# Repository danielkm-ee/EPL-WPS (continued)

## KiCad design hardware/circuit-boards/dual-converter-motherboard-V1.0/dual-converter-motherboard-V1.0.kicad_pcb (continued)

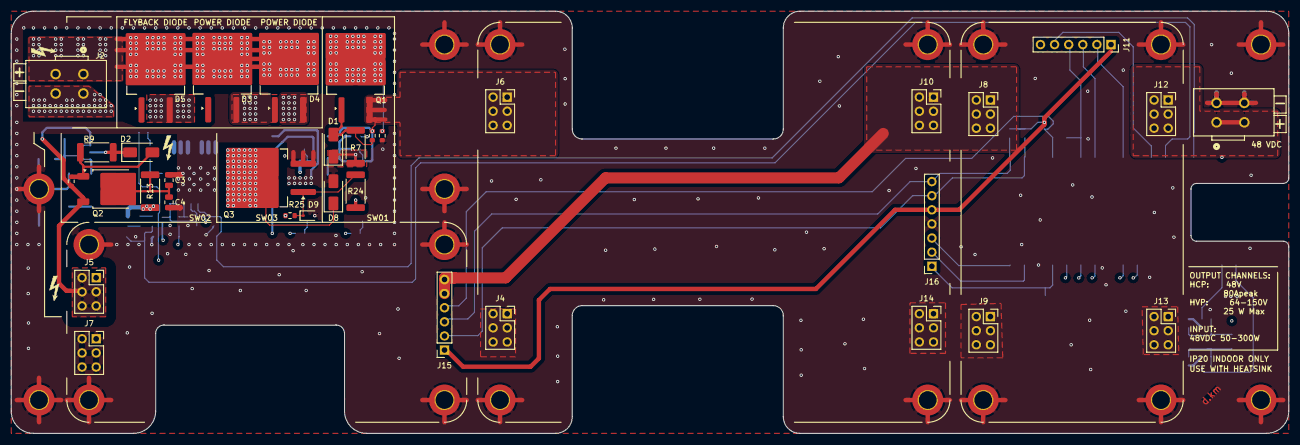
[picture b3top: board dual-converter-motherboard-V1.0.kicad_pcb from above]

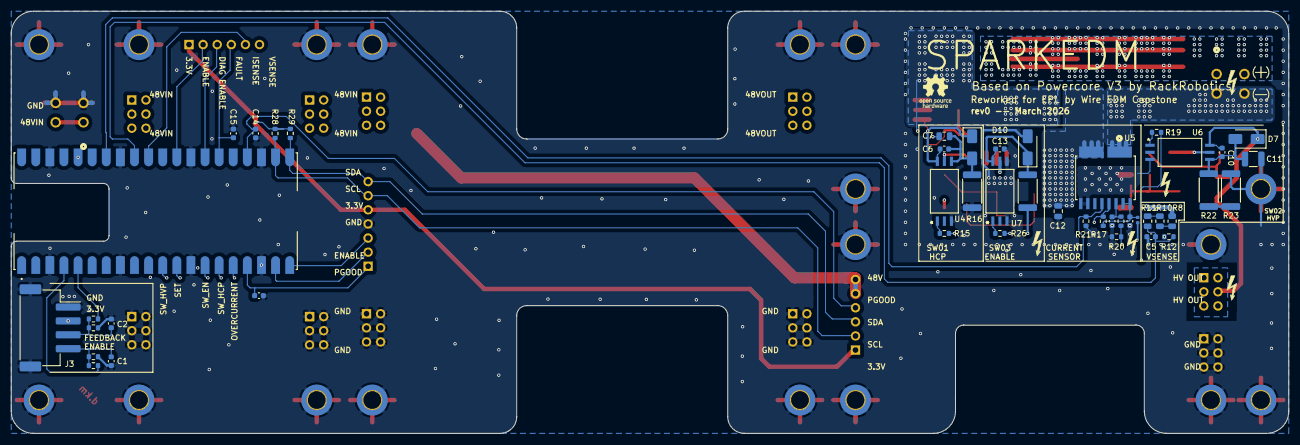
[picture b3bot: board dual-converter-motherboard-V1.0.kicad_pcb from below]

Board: 6 copper layers, 230.0 x 76.0 mm, 98 parts (45 on the bottom side), 49 nets.

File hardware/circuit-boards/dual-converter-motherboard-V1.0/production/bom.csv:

Designator,Footprint,Quantity,Value,LCSC Part #
"C1, C10, C13, C6, C8, C9",0603,6,220 nF,C726565
C11,1210,1,0.1 uF,C141218
"C14, C15, C16, C2",0603,4,10000 pF,C115056
C3,0805,1,10 nF,C342860
C7,0805,1,0.47 uF,C596323
"D1, D2, D8",D_SMA,3,US1M-13-F,C99333
"D10, D6, D7",D_SMA,3,D_Zener,C110525
"D3, D4, D5",STPSC20065GY-TR,3,STPSC20065GY-TR,C2965441
D9,D_SOD-323,1,D_Zener,C82043
"J1, J2",2601-1102,2,2601-1102,C7509568
"J10, J12, J13, J14, J4, J5, J6, J7, J8, J9",PinSocket_2x03_P2.54mm_Vertical,10,Conn_02x03_Odd_Even,
"J11, J15",PinSocket_1x06_P2.54mm_Vertical,2,Conn_01x06_Socket,
J16,PinSocket_1x07_P2.54mm_Vertical,1,Conn_01x07_Socket,
J3,S4B-XH-SM4-TB,1,S4B-XH-SM4-TB,C161861
L1,0402,1,BBUP00100505330Y00,C668299
Q1,SUM110P08-11L-E3,1,SUM110P08-11L-E3,C2838509
Q2,DMP45H4D9HK3-13,1,DMP45H4D9HK3-13,
Q3,TO-263-2,1,SIHB068N60EF-GE3,C3009875
"R1, R2",0603,2,1K,C22548
"R10, R11, R8",0805,3,332K,
"R12, R14, R17, R20, R21, R25, R3, R4",0603,8,10K,C20161635
R13,2512,1,1R,C840599
"R15, R19, R26",0603,3,100R,C20161635
"R16, R27",2512,2,1K,C7038808
"R18, R28, R29",0603,3,2.2K,C3032396
"R22, R23",2512,2,12K,C2082818
"R24, R7, R9",2512,3,10R,
"R5, R6",0603,2,255K,C295887
"U4, U6, U7",UCC23313BDWYR,3,UCC23313BDWYR,C2868027
U5,TMCS1133C3AQDVGR,1,TMCS1133C1A,C32266987
U8,SC0915,1,SC0915,C7203002

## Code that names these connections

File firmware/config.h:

/* config.h
 *
 * Pin assignments, hardware constants, and safe-operating limits for the
 * EPL Wire EDM Power Supply firmware. No runtime state belongs here.
 */

#ifndef EPL_WPS_CONFIG_H
#define EPL_WPS_CONFIG_H

#include <stdint.h>
#include <stdbool.h>

#ifdef __cplusplus
extern "C" {
#endif

/*=============================================================================
 * Pin assignments
 *===========================================================================*/
/* Digital I/O */
static const int EDM_ENABLE_PIN         = 2;    /* Digital input from motion controller */
static const int EDM_FEEDBACK_PIN       = 3;    /* PWM output to motion controller (power ratio) */
static const int OUTPUT_OVERCURRENT_PIN = 12;   /* Active-LOW comparator from output current sensor */
static const int BOOST_PGOOD_PIN        = 18;   /* Active-LOW power-good from boost-converter module */
static const int PMM_FAULT_PIN          = 20;   /* Active-LOW fault from power-management module */
static const int PMM_DIAG_EN_PIN        = 21;   /* Enables PMM fault reporting */
static const int PMM_ENABLE_PIN         = 22;   /* PMM high-side switch enable */
static const int STATUS_LED_PIN         = 25;   /* Onboard LED */

/* Output-stage PWM.
 * SW_HIGH_VOLTAGE_PHASE shares its PWM slice with OUTPUT_OVERCURRENT_SET;
 * SW_ENABLE shares with SW_HIGH_CURRENT_PHASE. P-channel switches invert
 * polarity so HIGH = OFF. */
static const int SW_HIGH_VOLTAGE_PHASE_PIN  = 8;   /* PWM 4A, P-channel (inverted) */
static const int OUTPUT_OVERCURRENT_SET_PIN = 9;   /* PWM 4B */
static const int SW_ENABLE_PIN              = 10;  /* PWM 5A, N-channel */
static const int SW_HIGH_CURRENT_PHASE_PIN  = 11;  /* PWM 5B, P-channel (inverted) */

/* Analog inputs */
static const int PMM_ISENSE_PIN    = 26;   /* PMM current sensor (200 mV/A); ADC channel 0 */
static const int OUTPUT_VSENSE_PIN = 27;   /* Output voltage via 99.6:1 divider; ADC channel 1 */
static const int OUTPUT_ISENSE_PIN = 28;   /* Output current sensor TMCS1133 (25 mV/A); ADC channel 2 */

/* I2C (boost-converter DPOT) */
static const int I2C_SDA_PIN = 16;
static const int I2C_SCL_PIN = 17;

/*=============================================================================
 * Hardware constants
 *===========================================================================*/
#define I2C_PORT             i2c0
#define DPOT_ADDR            0x3E
#define DPOT_REG             0x00
#define I2C_BAUD_RATE_HZ     10000

/* Array-size constants must be #define, not static const, for use in C
 * array declarators and struct definitions. */
#define DEVICE_CURRENT_BUFFER_SIZE  100
#define BOOST_DPOT_POSITION_MAX     110
#define MAX_CMD_PARAMS              4

static const int      ADC_RESOLUTION_BITS = 12;
static const uint32_t PWM_BASE_CLOCK_FREQ = 133000000;  /* 133 MHz */

/* EDM_FEEDBACK encodes input-power ratio as PWM frequency at a fixed
 * 50% duty cycle. Range is narrow on purpose: at MIN the period
 * (5 ms) is shorter than the 10 ms firmware update interval, so the
 * host sees at least two full cycles between updates - resolution
 * traded for responsiveness. See docs/freq-encoding.md. */
static const uint16_t EDM_FEEDBACK_PWM_CLOCK_DIVIDER = 64;
static const float    EDM_FEEDBACK_PWM_DUTY          = 0.5f;
static const uint32_t EDM_FEEDBACK_FREQ_MIN_HZ       = 200;
static const uint32_t EDM_FEEDBACK_FREQ_MAX_HZ       = 400;

/*=============================================================================
 * Sensor scaling
 *===========================================================================*/
static const float ADC_TO_VOLTS                = 3.3f / 4095.0f;
static const float PMM_ISENSE_V_PER_AMP        = 0.200f;      /* PMM current sensor */
static const float ISENSE_OUTPUT_V_PER_AMP     = 0.025f;      /* TMCS1133C1A */
static const int   ISENSE_OUTPUT_AMPS_PER_VOLT = 40;
static const float OUTPUT_VOLTAGE_SCALE        = 0.08090972f; /* (3.3/4095) * 100.4 */

static const int PMM_CALIBRATION_SAMPLES    = 100;
static const int PMM_CALIBRATION_DELAY_MS   = 1;
static const int OUTPUT_CURRENT_SENSOR_CALIBRATION_SAMPLES  = 100;
static const int OUTPUT_CURRENT_SENSOR_CALIBRATION_DELAY_MS = 1;

/*=============================================================================
 * Safe-operating limits
 *===========================================================================*/
static const float MAX_SAFE_INPUT_CURRENT         = 7.3f;   /* A */
static const float MAX_INPUT_POWER_SETPOINT_WATTS = 75.0f;  /* W */
static const float INPUT_SUPPLY_VOLTAGE           = 48.0f;  /* V (nominal) */

static const int MIN_HIGH_VOLTAGE_PHASE_VOLTS = 64;
static const int MAX_HIGH_VOLTAGE_PHASE_VOLTS = 100;

static const int BOOST_DPOT_POSITION_MIN         = 0;
static const int BOOST_CONVERTER_RAMP_SPACING_MS = 10;

static const float MIN_DUTY_CYCLE             = 0.01f;
static const float MAX_DUTY_CYCLE             = 0.12f;
static const float MIN_MACHINING_FREQUENCY_HZ = 5000.0f;
static const float MAX_MACHINING_FREQUENCY_HZ = 10000.0f;
static const float MIN_ON_TIME_MICROS         = 1.000f;
static const float MAX_ON_TIME_MICROS         = 25.000f;
static const float MIN_OFF_TIME_MICROS        = 88.000f;
static const float MIN_INIT_VOLTAGE           = 64.0f;  /* MIN_HIGH_VOLTAGE_PHASE_VOLTS */
static const float MAX_INIT_VOLTAGE           = 100.0f; /* MAX_HIGH_VOLTAGE_PHASE_VOLTS */

static const int DEFAULT_OUTPUT_CURRENT_THRESHOLD_A = 8;

/* EDM iso-frequency: success-rate calculation window and pulse-skip threshold. */
static const int    DISCHARGES_PER_CALC_INTERVAL         = 10;
static const double MAX_DISCHARGE_SUCCESS_RATE_THRESHOLD = 0.800;

/* EDM Iso-frequency mode: HV pulse on-time and PWM phase offset to prevent
 * shoot-through between SW_HIGH_VOLTAGE_PHASE and SW_ENABLE. */
static const int    EDM_ISOFREQ_HV_PULSE_ON_TIME_US = 1;
static const double EDM_ISOFREQ_HV_PWM_OFFSET       = 0.25;

/*=============================================================================
 * Timing & feature flags
 *===========================================================================*/
static const int  PMM_INRUSH_DELAY_MS      = 500;
static const int  PERIPH_MGMT_INTERVAL_MS  = 10;
static const int  TELEMETRY_INTERVAL_MS    = 1000;

static const bool PERIODIC_TELEMETRY_ENABLED          = true;
static const bool ALLOW_DISCHARGE_SUCCESS_RATE_PULSE_SKIP = true;
static const bool ALLOW_POWER_SETPOINT_PULSE_SKIP     = true;

#ifdef __cplusplus
}
#endif

#endif /* EPL_WPS_CONFIG_H */

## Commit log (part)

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2026-04-11 update license and remove trademarked terms, update attribution
2026-04-11 begin firmware reworks with new project structure
2026-04-14 begin cleanup of code, document potential simplifications/optimizations
2026-04-14 remove session.vim (local paths in file)
2026-04-20 add digital potentiometer test
2026-04-21 documenting firmware operation
2026-04-21 add init file for claude
2026-04-25 docs: make docs folder in firmware, include refactor report and new library docs generated using opus
2026-04-25 refactor: updating new refactored source code for validation and testing
2026-04-25 update CLAUDE.md with instructions on formatting, coding philosophy, codestyle
2026-04-25 add skim skill (demo)
2026-04-25 add firmware readme and setup instructions
2026-04-25 move readme to firmware root, update refactor report
2026-04-25 update setup instructions
2026-04-25 fix: formatting mistake in firmware readme
2026-04-26 implementing boost converter struct for api, adding calibration system for dpot. todo:make cal table private
2026-04-26 update sensor functions, new implementation
2026-04-26 update main firmware file and telemetry to use new library
2026-04-26 update boost converter config, use naming scheme
2026-04-26 add dev notes
2026-04-26 give claude compile and flashing instructions
2026-04-27 working on sensor module, warning: currently broken
2026-04-28 Revert "working on sensor module, warning: currently broken"
    This reverts commit 1827d26e5842b240438f25bb21ef2ef30b65d1c3.
2026-04-28 Revert "Revert "working on sensor module, warning: currently broken"" Bring refactor branch back to compiling/running state
    This reverts commit 237029e37f75e89845acd283399535b34020cad1.
2026-04-30 add output stage handling to voltage table initialization in setup()
2026-04-30 update PIN constant names, add print statements for boost converter setup sequence
2026-05-07 new src, library style implementation, removed dependancy on arduino-pico and rely on pico-sdk only.
2026-05-07 replace firmware.ino with main.c, add pico-sdk based build system and new config
2026-05-07 update library reference and README to represent new runtime logic and library implementation
2026-05-07 add low-voltage error check for HVP
2026-05-07 add set_telemetry <on/off> command to disable continuous telemetry updates
2026-05-24 add session.vim to gitignore
2026-06-05 add wps-monitor tool for ease-of-use of the EDM supply
2026-06-05 move docs from readme, consolidate readme.
